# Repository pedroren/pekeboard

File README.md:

# PeKeboard
PeKeboard and PeKepad

## Idea
The idea was to create a split keyboard without losing some of the occasional keys for miscellaneous or occasional use, like the Function, Media keys and Arrow keys.

I took inspiration (and was about to build) on the Apiaster keyboard (https://github.com/nmunnich/apiaster) and the Soffle variant Souffle (https://github.com/climent/SouffleKeyboard).

So I decided to create a three part keyboard, composed of a pair of split sides, left and right; and a central Macropad, containing the Function and Arrows keys, and a pair of rotary encoders. This central/macropad also doubles as the Dongle, containing a display to show layer and peripherals battery information.

## Tools
- Ergogen
- Kicad
- freerouting

## Folders structure
- layout_keymap:
- pekeboard
- pekepad
- pekepad-v
- zmk-firmware
- rmk_firmware
- release
- kicad

## Subfolders
- cases
- footprints
- pcbs

## Build guide
see build_guide.md

## Todo

## Referenced libraries

- ZMK
- zmk-dongle-display (https://github.com/englmaxi/zmk-dongle-display)
- zmk-feature-status-led (https://github.com/sekigon-gonnoc/zmk-feature-status-led)

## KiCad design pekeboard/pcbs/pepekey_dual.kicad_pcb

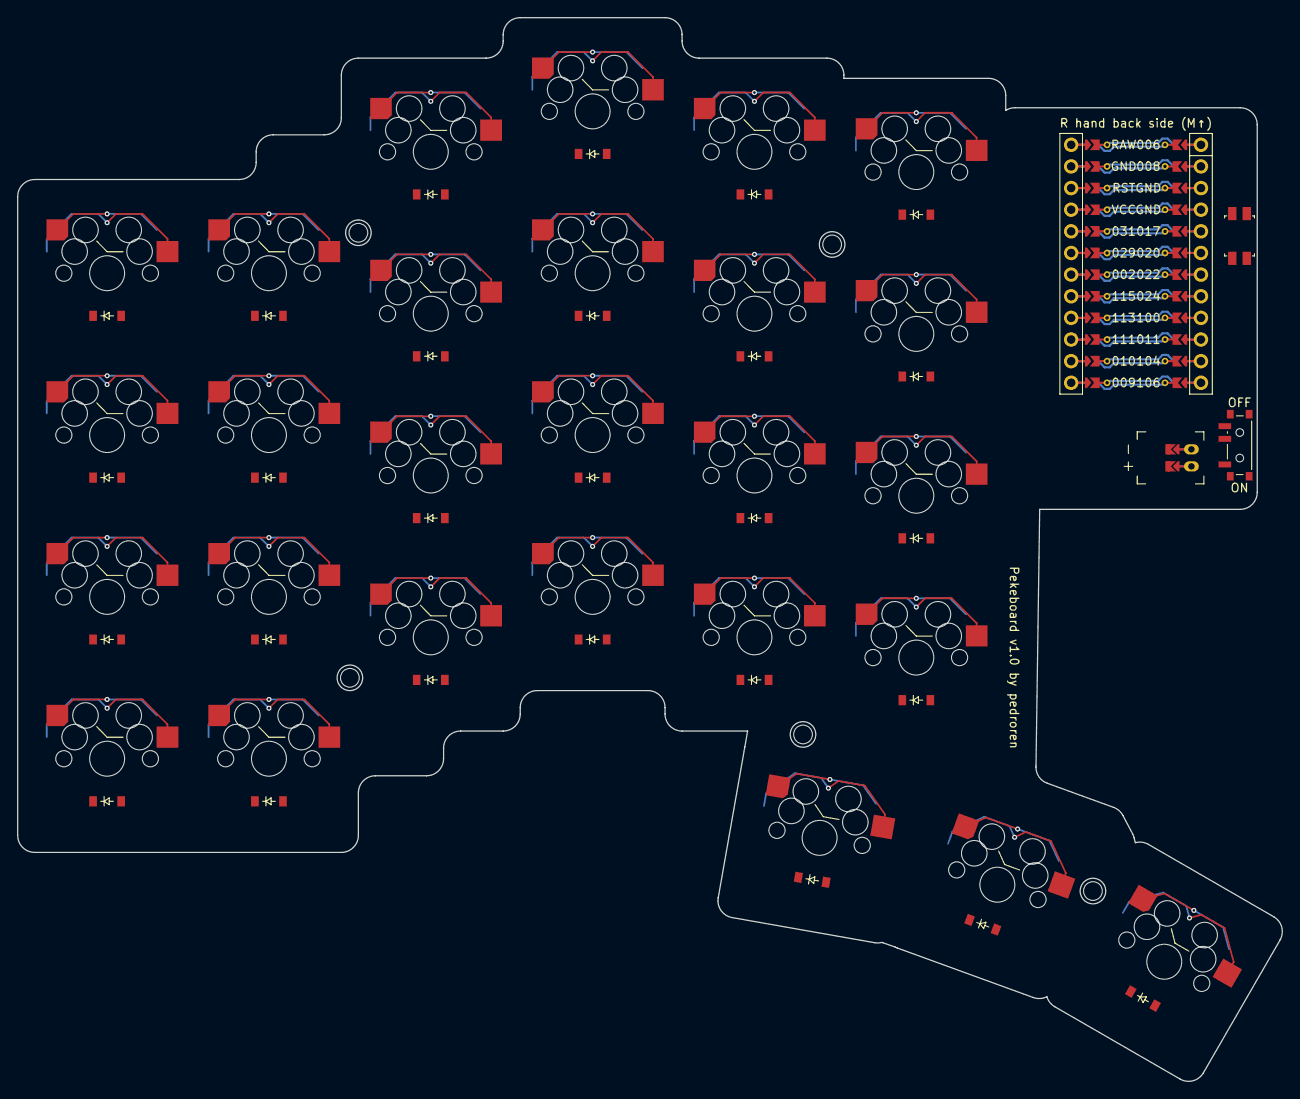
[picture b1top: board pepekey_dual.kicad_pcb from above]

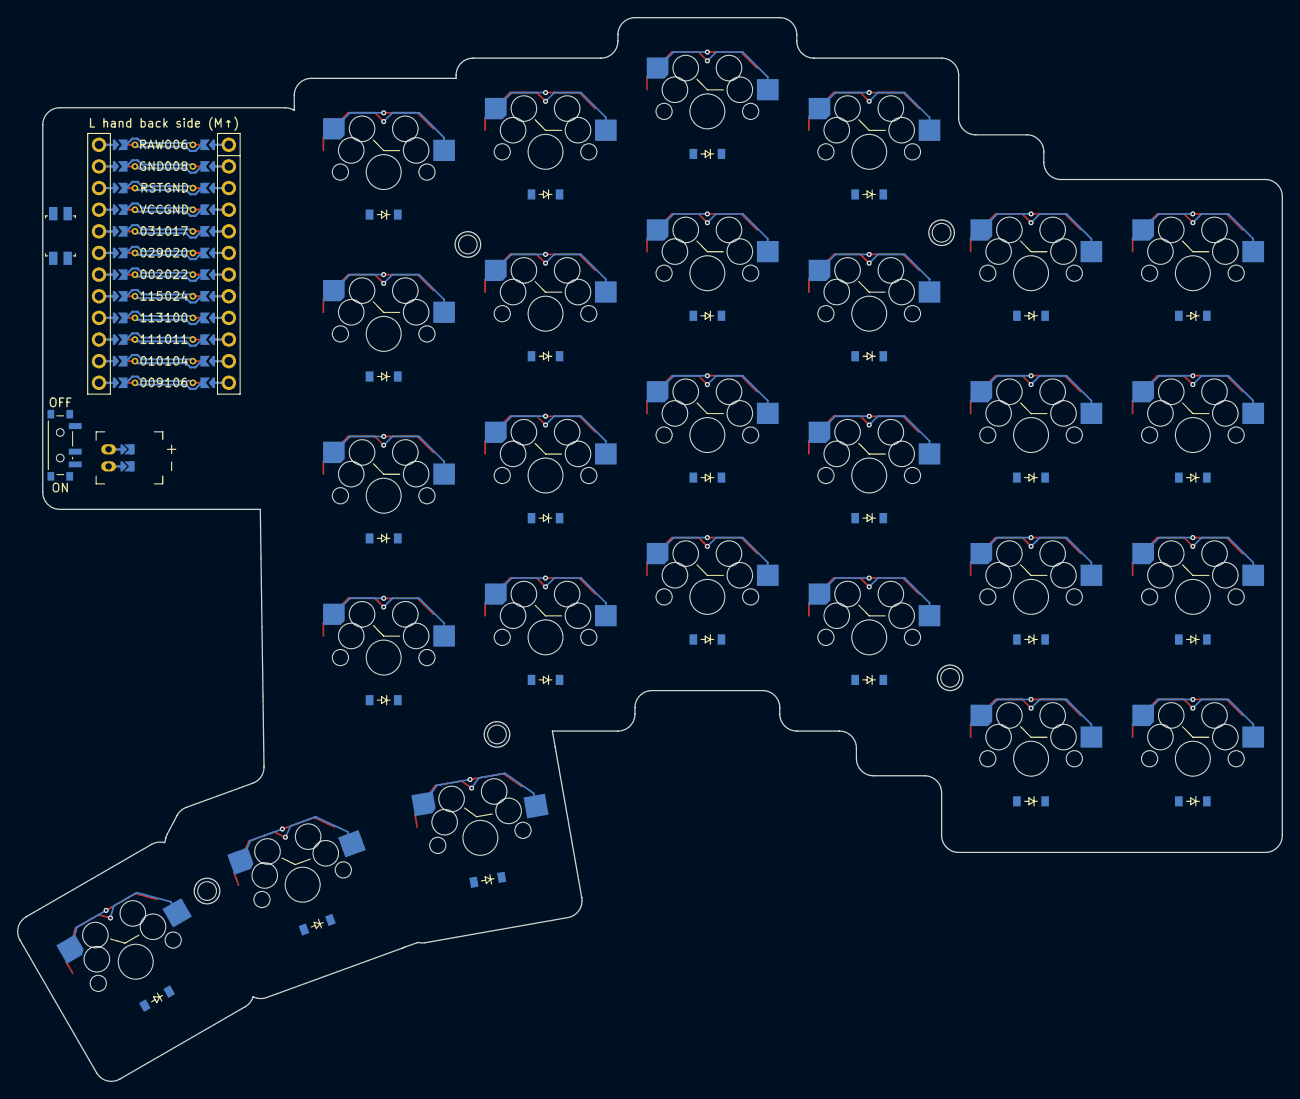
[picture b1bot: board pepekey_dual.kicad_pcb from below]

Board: 2 copper layers, 148.5 x 124.9 mm, 63 parts (27 on the bottom side), 45 nets.

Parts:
D1, D2, D3, D4, D5, D6, D7, D8, D9, D10, D11, D12, D13, D14, D15, D16, D17, D18, D19, D20, D21, D22, D23, D24, D25, D26, D27: diode_tht_sod123
JST1: battery_connector_jst_ph_2
MCU1: mcu_nice_nano
MH1, MH2, MH3, MH4, MH5: mounting_hole_npth
PWR1: power_switch_smd_side
RST1: reset_switch_smd_side
S1, S2, S3, S4, S5, S6, S7, S8, S9, S10, S11, S12, S13, S14, S15, S16, S17, S18, S19, S20, S21, S22, S23, S24, S25, S26, S27: switch_mx

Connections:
BAT_P: JST1.1, PWR1.1, PWR1.3
GND: JST1.2, MCU1.103, MCU1.104, MCU1.123, RST1.1, RST1.3
JST1_1: JST1.11, JST1.21, JST1.31
JST1_2: JST1.12, JST1.22, JST1.32
P002: D3.1, D7.1, D11.1, D15.1, D19.1, D23.1, MCU1.118
P008: MCU1.102, S1.1, S2.1, S3.1, S4.1
P011: MCU1.110, S17.1, S18.1, S19.1, S20.1, S25.1
P022: MCU1.107, S5.1, S6.1, S7.1, S8.1
P024: MCU1.108, S9.1, S10.1, S11.1, S12.1
P029: D2.1, D6.1, D10.1, D14.1, D18.1, D22.1, MCU1.119
P031: D1.1, D5.1, D9.1, D13.1, D17.1, D21.1, MCU1.120
P100: MCU1.109, S13.1, S14.1, S15.1, S16.1
P106: MCU1.112, S21.1, S22.1, S23.1, S24.1, S26.1
P111: MCU1.115, S27.1
P113: D25.1, D26.1, D27.1, MCU1.116
P115: D4.1, D8.1, D12.1, D16.1, D20.1, D24.1, MCU1.117
RAW: MCU1.124, PWR1.2
RST: MCU1.122, RST1.2, RST1.4
index_bottom: D17.2, S17.2
index_home: D18.2, S18.2
index_num: D20.2, S20.2
index_top: D19.2, S19.2
inner_bottom: D21.2, S21.2
inner_home: D22.2, S22.2
inner_num: D24.2, S24.2
inner_thumbrow: D27.2, S27.2
inner_top: D23.2, S23.2
middle_bottom: D13.2, S13.2
middle_home: D14.2, S14.2
middle_num: D16.2, S16.2
middle_thumbrow: D26.2, S26.2
middle_top: D15.2, S15.2
outer_bottom: D1.2, S1.2
outer_home: D2.2, S2.2
outer_num: D4.2, S4.2
outer_thumbrow: D25.2, S25.2
outer_top: D3.2, S3.2
pinky_bottom: D5.2, S5.2
pinky_home: D6.2, S6.2
pinky_num: D8.2, S8.2
pinky_top: D7.2, S7.2
ring_bottom: D9.2, S9.2
ring_home: D10.2, S10.2
ring_num: D12.2, S12.2
ring_top: D11.2, S11.2

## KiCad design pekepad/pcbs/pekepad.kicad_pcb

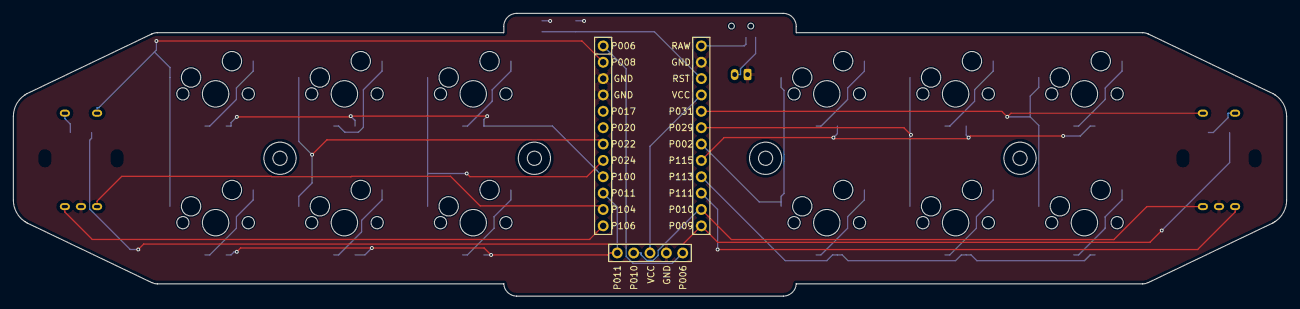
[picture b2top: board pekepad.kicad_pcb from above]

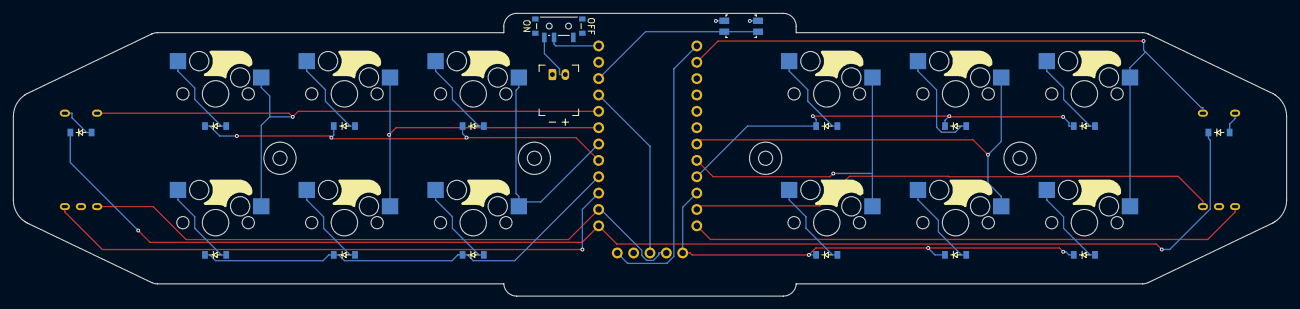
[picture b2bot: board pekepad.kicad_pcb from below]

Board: 2 copper layers, 197.7 x 43.9 mm, 37 parts (29 on the bottom side), 35 nets.

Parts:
D1, D2, D3, D4, D5, D6, D7, D8, D9, D10, D11, D12, D13, D14: diode_tht_sod123
DISP1: display_nice_view
JST1: battery_connector_jst_ph_2
MCU1: mcu_nice_nano
MH1, MH2, MH3, MH4: mounting_hole_npth
PWR1: power_switch_smd_side
RE1, RE2: rotary_encoder_ec11_ec12
RST1: reset_switch_smd_side
S1, S2, S3, S4, S5, S6, S7, S8, S9, S10, S11, S12: switch_mx

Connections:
BAT_P: JST1.2, PWR1.3
GND: DISP1.4, JST1.1, MCU1.2, MCU1.21, MCU1.22, RE1.B, RE2.B, RST1.1, RST1.3
P002: MCU1.7, S11.1, S12.1
P006: DISP1.5, MCU1.24
P008: MCU1.23, RE1.S2, S1.1, S2.1
P009: D13.1, D14.1, MCU1.12
P010: DISP1.2, MCU1.11, RE2.C
P011: D1.1, D3.1, D5.1, DISP1.1, MCU1.15
P022: MCU1.18, S3.1, S4.1
P024: MCU1.17, S5.1, S6.1
P029: MCU1.6, S9.1, S10.1
P031: MCU1.5, RE2.S1, S7.1, S8.1
P100: D2.1, D4.1, D6.1, MCU1.16
P104: MCU1.14, RE1.A
P106: MCU1.13, RE1.C
P111: MCU1.10, RE2.A
P113: D7.1, D9.1, D11.1, MCU1.9
P115: D8.1, D10.1, D12.1, MCU1.8
RAW: MCU1.1, PWR1.2
RST: MCU1.3, RST1.2, RST1.4
VCC: DISP1.3, MCU1.4
enccol_encrow: D13.2, RE1.S1
inner_bottom: D5.2, S5.2
inner_top: D6.2, S6.2
middle_bottom: D3.2, S3.2
middle_top: D4.2, S4.2
mirror_enccol_encrow: D14.2, RE2.S2
mirror_inner_bottom: D11.2, S11.2
mirror_inner_top: D12.2, S12.2
mirror_middle_bottom: D9.2, S9.2
mirror_middle_top: D10.2, S10.2
mirror_outer_bottom: D7.2, S7.2
mirror_outer_top: D8.2, S8.2
outer_bottom: D1.2, S1.2
outer_top: D2.2, S2.2

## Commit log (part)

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2026-03-02 draft
2026-03-05 batt connector space fix
2026-03-06 Freeing up Pin P1 (SC) for Nice View Adding some 3D models for kicad
2026-03-09 Ergogen: Updating assigned pins Ergogen: Renaming pins names to NiceNano Pings RMK: Updating assigned pins RMK: Always clear storage, temporary RMK: Trying to fix vial layout
2026-03-09 Ergogen: increasing encoder hole
2026-03-09 Adding keyboard editor json and fixing vial layout
2026-03-11 Inner case verical spacing Cutout for USB, reset and power Switchplate sides support
2026-03-11 Adjusting case inner space
2026-03-11 More case fixes
2026-03-12 More fixes to the case/pcb/plate
2026-03-12 forgot pcb wiring
2026-03-12 nice view display experim ent
2026-03-12 adjusting I2C/SPI pins
2026-03-12 rust settings
2026-03-14 experiments
2026-03-15 remove hardcoded ceoloide
2026-03-15 ceoloide as submodule
2026-03-15 Reorganizing kicad common folder
2026-03-15 reorganizing kicad custom footprints
2026-03-15 Missing encoder cutout on plate
2026-03-16 work on keyboard
2026-03-17 Fixing macropad plate mcu cutout
2026-03-17 improvements
2026-03-21 Ajusting plate mcu cutout mcu is now a point of reference
2026-03-29 rmk: encoder step fix. zmk firmware.
2026-03-29 same
2026-03-29 encoder fix
2026-04-04 pekeboard cases
2026-04-05 pekeboard case refinement and cutouts
2026-04-05 Battery area and cover
2026-04-05 Fixing keys spacing More case and battery space refinements
2026-04-05 reducing pcb padding
2026-04-06 Extreme trimming
2026-04-06 Sandwich style bottom case
2026-04-07 Adjusting mounting holes
2026-04-08 Bump version and enable reversible pcb
    Updated version to 0.1.0 and set reversible pcb parameters to true.
2026-04-09 Fix mounting hole outside PCB
2026-04-09 reversible diodes removing fill zone
2026-04-11 Fix pekeboard sandwich case "walls"
2026-04-11 pekepad vertical version
2026-04-11 updated keymap images
2026-04-11 pekepadv
2026-04-12 pekepad folder fix
2026-04-12 ceoloide submodule for pekepadv
2026-04-14 pekeboard case small adjustments
2026-04-14 Less spread for thumb cluster
2026-04-14 reorganizing case
2026-04-14 kicad gitignore
2026-04-14 reorganizing folders
2026-04-14 renaming macropad folder
2026-04-14 folder adjustments
2026-04-15 verifications
2026-04-15 updating generated files
2026-04-15 switchplate fix
2026-04-16 Moving battery connector to Front
2026-05-12 Removing pcb mounting hole, only screw Adding plate support o-rings
2026-06-07 - Switching to non-reversible pcb left and right sides - Fix invalid pin - 3D model for MX switches
2026-06-07 Adjusting thumbs pin to allow autorouting
2026-06-07 Removing right side for Cases section
2026-06-08 more spacing for routing
2026-06-12 pcb label
2026-06-12 submodule ref
2026-06-13 Version label and rerouting
2026-06-18 V1.0 Fabrication sent to JLCPCB
2026-06-18 JLCPCB fabrication ready
2026-06-18 case adjustment for new PCB dimensions
2026-06-26 pekeboard: Reducing battery cover, adding top gasket
2026-06-26 gitignore
2026-06-27 restoring reversible PCB option
2026-06-27 controller_cover
